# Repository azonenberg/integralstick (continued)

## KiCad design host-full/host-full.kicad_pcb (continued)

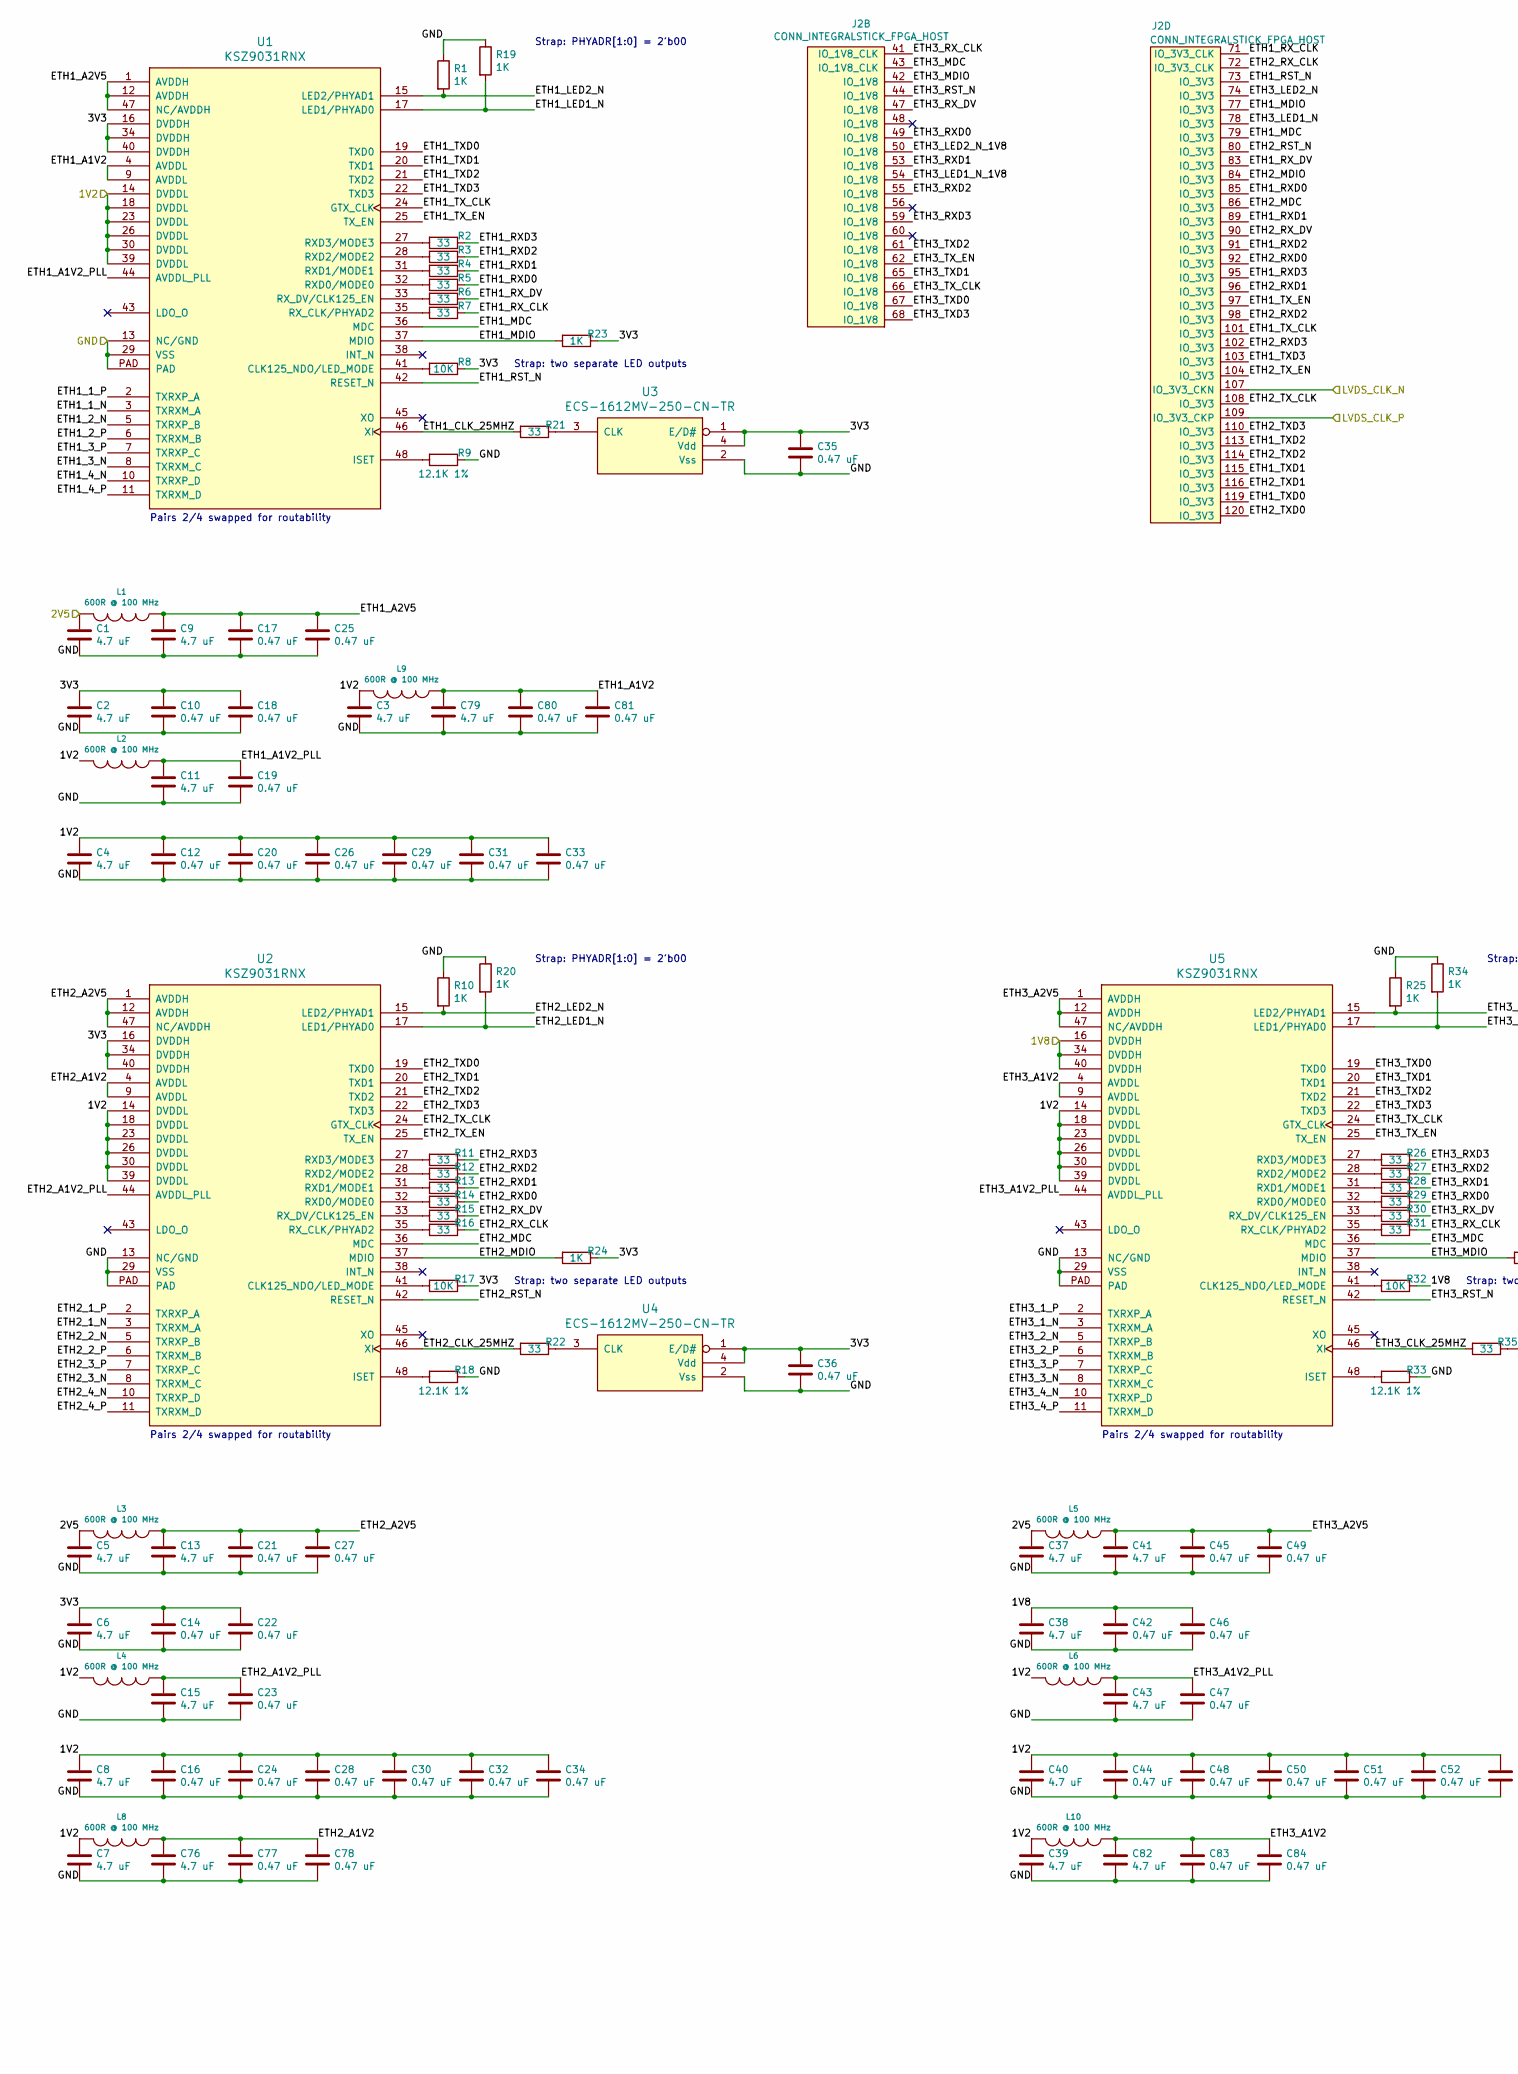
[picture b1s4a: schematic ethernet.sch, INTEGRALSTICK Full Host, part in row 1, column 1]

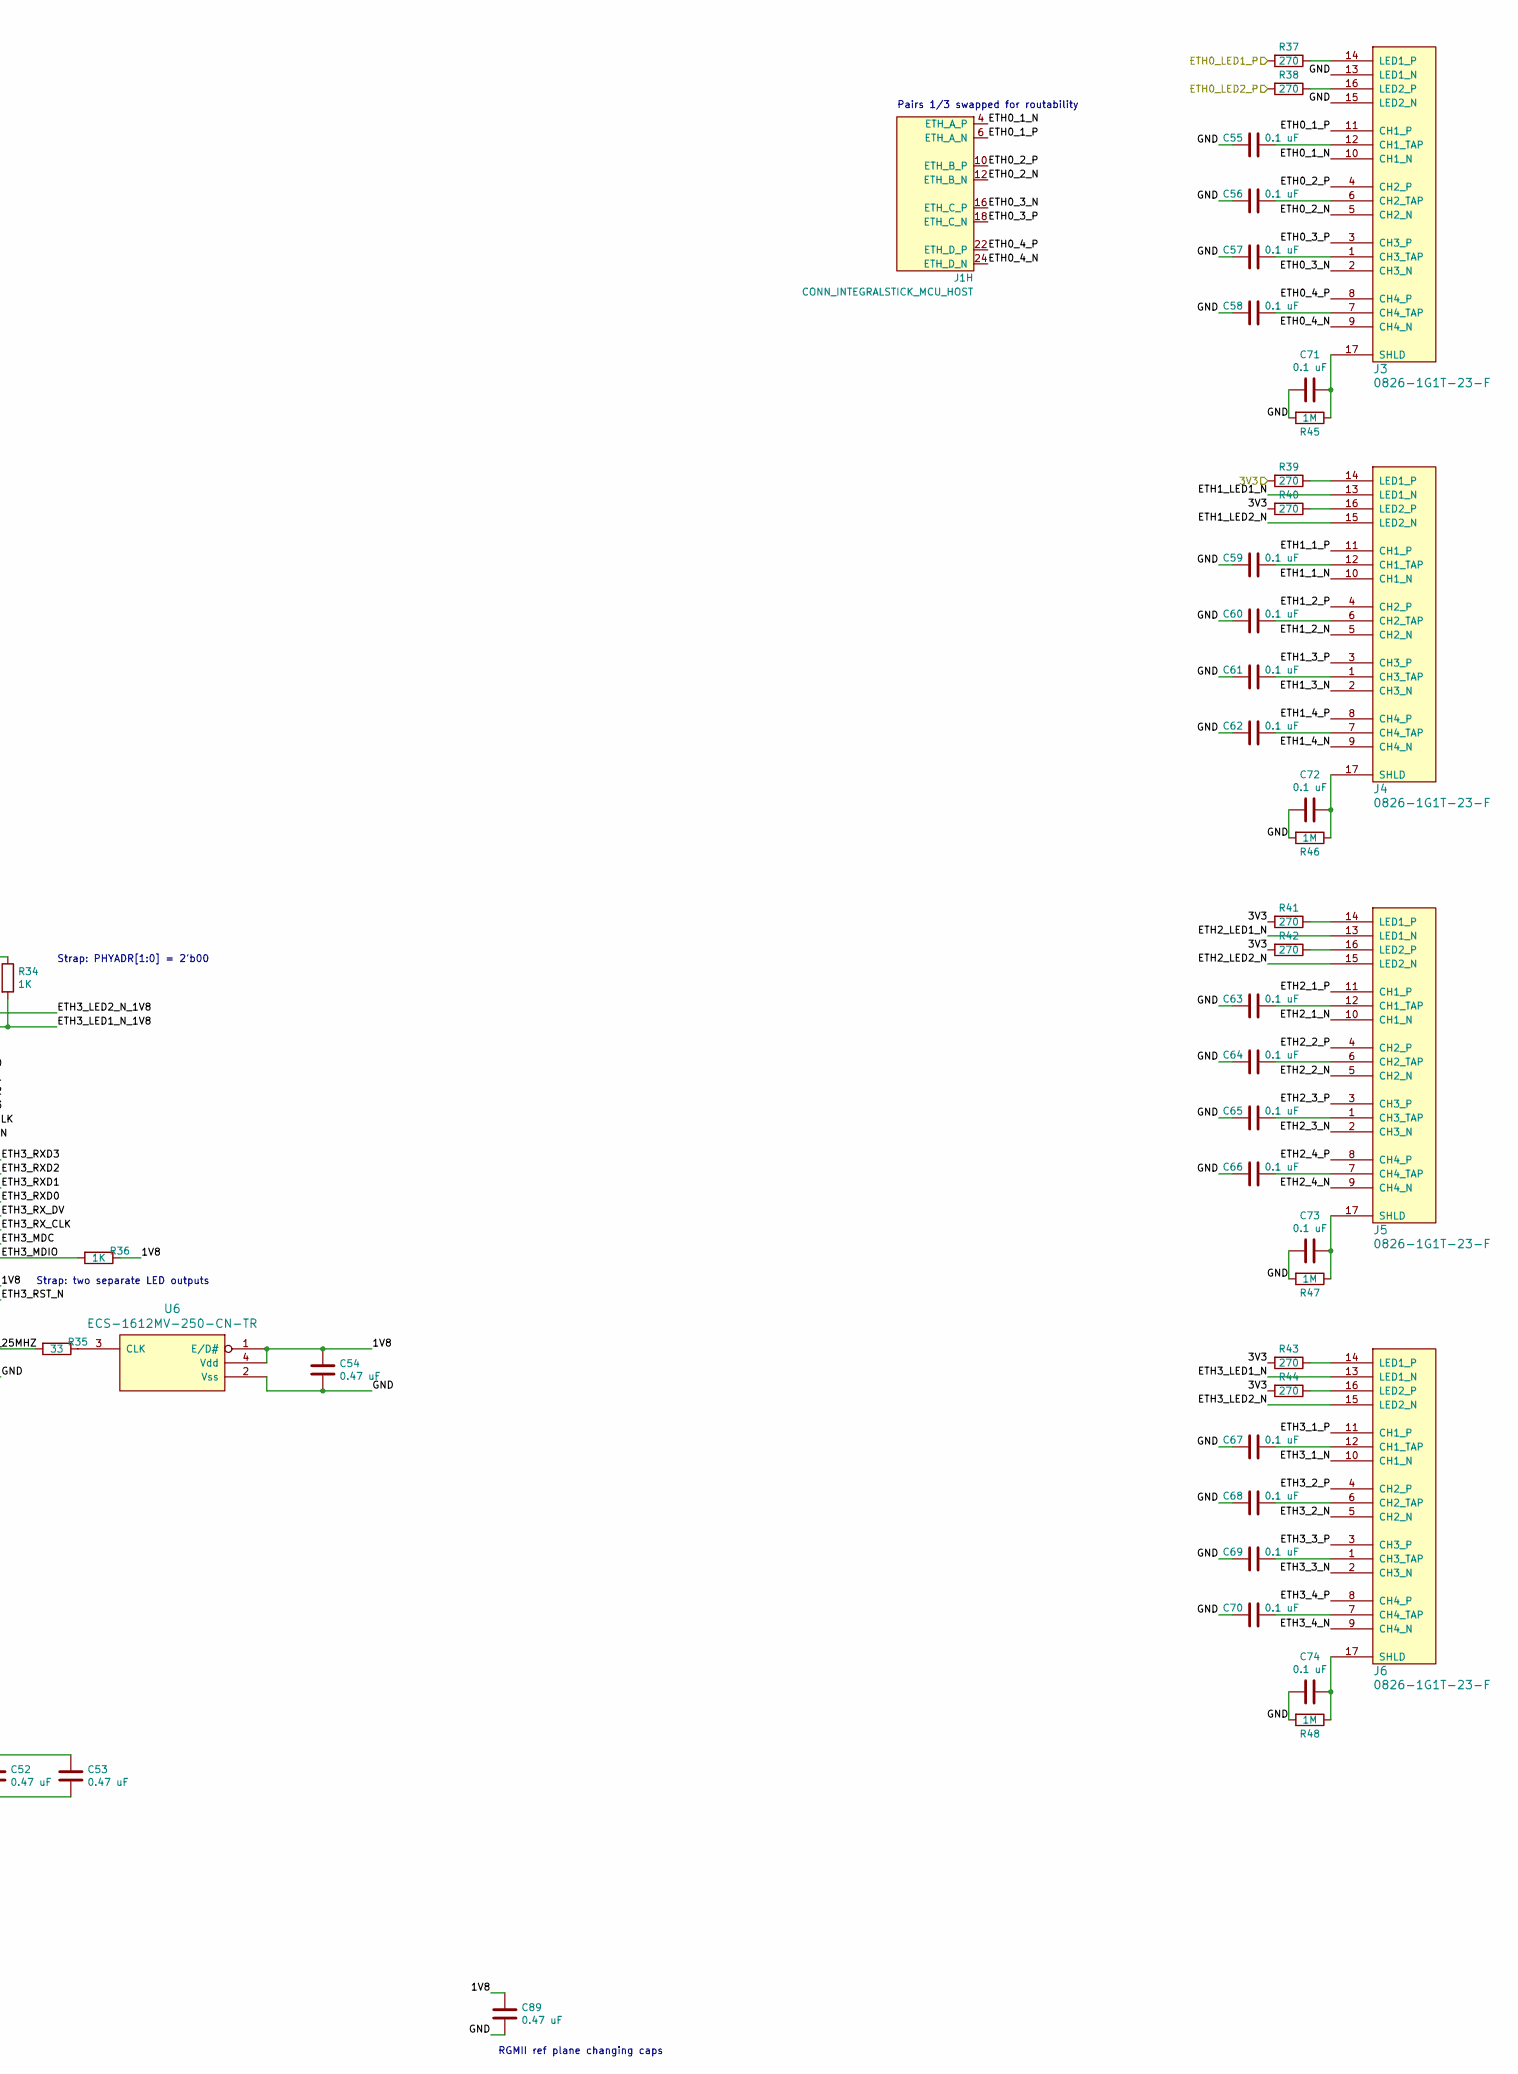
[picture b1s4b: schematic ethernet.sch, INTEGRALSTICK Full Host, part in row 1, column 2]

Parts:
C1, C2, C3, C4, C5, C6, C7, C8, C9, C11, C13, C15, C37, C38, C39, C40, C41, C43, C76, C79, C82: 4.7 uF; EIA_0603_CAP_NOSILK
C10, C12, C14, C16, C17, C18, C19, C20, C21, C22, C23, C24, C25, C26, C27, C28, C29, C30, C31, C32, C33, C34, C35, C36, C42, C44, C45, C46, C47, C48, C49, C50, C51, C52, C53, C54, C77, C78, C80, C81, C83, C84, C89: 0.47 uF; EIA_0402_CAP_NOSILK
C55, C56, C57, C58, C59, C60, C61, C62, C63, C64, C65, C66, C67, C68, C69, C70, C71, C72, C73, C74: 0.1 uF; EIA_0402_CAP_NOSILK
J1: CONN_INTEGRALSTICK_MCU_HOST; CONN_SAMTEC_QSH-060-01-L-D-A
J2: CONN_INTEGRALSTICK_FPGA_HOST; CONN_SAMTEC_QSH-060-01-L-D-A
J3, J4, J5, J6: 0826-1G1T-23-F; CONN_BELFUSE_0826_1G1T_23_F
L1, L2, L3, L4, L5, L6, L8, L9, L10: 600R @ 100 MHz; EIA_0402_CAP_NOSILK
R1, R10, R19, R20, R23, R24, R25, R34, R36: 1K; EIA_0402_RES_NOSILK
R2, R3, R4, R5, R6, R7, R11, R12, R13, R14, R15, R16, R21, R22, R26, R27, R28, R29, R30, R31, R35: 33; EIA_0402_RES_NOSILK
R8, R17, R32: 10K; EIA_0402_RES_NOSILK
R9, R18, R33: 12.1K 1%; EIA_0402_RES_NOSILK
R37, R38, R39, R40, R41, R42, R43, R44: 270; EIA_0402_RES_NOSILK
R45, R46, R47, R48: 1M; EIA_0402_RES_NOSILK
U1, U2, U5: KSZ9031RNX; QFN_48_0.5MM_7x7MM
U3, U4, U6: ECS-1612MV-250-CN-TR; OSCILLATOR_1.6x1.2

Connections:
/1V2: C3.1, C4.1, C7.1, C8.1, C12.1, C16.1, C20.1, C24.1, C26.1, C28.1, C29.1, C30.1, C31.1, C32.1, C33.1, C34.1, C39.1, C40.1, C44.1, C48.1, C50.1, C51.1, C52.1, C53.1, L2.2, L4.2, L6.2, L8.2, L9.2, L10.2, U1.14 (DVDDL), U1.18 (DVDDL), U1.23 (DVDDL), U1.26 (DVDDL), U1.30 (DVDDL), U1.39 (DVDDL), U2.14 (DVDDL), U2.18 (DVDDL), U2.23 (DVDDL), U2.26 (DVDDL), U2.30 (DVDDL), U2.39 (DVDDL), U5.14 (DVDDL), U5.18 (DVDDL), U5.23 (DVDDL), U5.26 (DVDDL), U5.30 (DVDDL), U5.39 (DVDDL); also elsewhere on the board
/1V8: C38.1, C42.1, C46.1, C54.1, C89.1, R32.1, R36.1, U5.16 (DVDDH), U5.34 (DVDDH), U5.40 (DVDDH), U6.1 (E/D#), U6.4 (Vdd); also elsewhere on the board
/2V5: C1.1, C5.1, C37.1, L1.2, L3.2, L5.2; also elsewhere on the board
/3V3: C2.1, C6.1, C10.1, C14.1, C18.1, C22.1, C35.1, C36.1, R8.1, R17.1, R23.1, R24.1, R39.2, R40.2, R41.2, R42.2, R43.2, R44.2, U1.16 (DVDDH), U1.34 (DVDDH), U1.40 (DVDDH), U2.16 (DVDDH), U2.34 (DVDDH), U2.40 (DVDDH), U3.1 (E/D#), U3.4 (Vdd), U4.1 (E/D#), U4.4 (Vdd); also elsewhere on the board
/ETH0_LED1_P: R37.2; also elsewhere on the board
/ETH0_LED2_P: R38.2; also elsewhere on the board
/Ethernet/ETH0_1_N: J1.4 (ETH_A_P), J3.10 (CH1_N)
/Ethernet/ETH0_1_P: J1.6 (ETH_A_N), J3.11 (CH1_P)
/Ethernet/ETH0_2_N: J1.12 (ETH_B_N), J3.5 (CH2_N)
/Ethernet/ETH0_2_P: J1.10 (ETH_B_P), J3.4 (CH2_P)
/Ethernet/ETH0_3_N: J1.16 (ETH_C_P), J3.2 (CH3_N)
/Ethernet/ETH0_3_P: J1.18 (ETH_C_N), J3.3 (CH3_P)
/Ethernet/ETH0_4_N: J1.24 (ETH_D_N), J3.9 (CH4_N)
/Ethernet/ETH0_4_P: J1.22 (ETH_D_P), J3.8 (CH4_P)
/Ethernet/ETH1_1_N: J4.10 (CH1_N), U1.3 (TXRXM_A)
/Ethernet/ETH1_1_P: J4.11 (CH1_P), U1.2 (TXRXP_A)
/Ethernet/ETH1_2_N: J4.5 (CH2_N), U1.5 (TXRXP_B)
/Ethernet/ETH1_2_P: J4.4 (CH2_P), U1.6 (TXRXM_B)
/Ethernet/ETH1_3_N: J4.2 (CH3_N), U1.8 (TXRXM_C)
/Ethernet/ETH1_3_P: J4.3 (CH3_P), U1.7 (TXRXP_C)
/Ethernet/ETH1_4_N: J4.9 (CH4_N), U1.10 (TXRXP_D)
/Ethernet/ETH1_4_P: J4.8 (CH4_P), U1.11 (TXRXM_D)
/Ethernet/ETH1_A1V2: C79.1, C80.1, C81.1, L9.1, U1.4 (AVDDL), U1.9 (AVDDL)
/Ethernet/ETH1_A1V2_PLL: C11.1, C19.1, L2.1, U1.44 (AVDDL_PLL)
/Ethernet/ETH1_A2V5: C9.1, C17.1, C25.1, L1.1, U1.1 (AVDDH), U1.12 (AVDDH), U1.47 (NC/AVDDH)
/Ethernet/ETH1_CLK_25MHZ: R21.2, U1.46 (XI)
/Ethernet/ETH1_LED1_N: J4.13 (LED1_N), R19.2, U1.17 (LED1/PHYAD0)
/Ethernet/ETH1_LED2_N: J4.15 (LED2_N), R1.2, U1.15 (LED2/PHYAD1)
/Ethernet/ETH1_MDC: J2.79 (IO_3V3), U1.36 (MDC)
/Ethernet/ETH1_MDIO: J2.77 (IO_3V3), R23.2, U1.37 (MDIO)
/Ethernet/ETH1_RST_N: J2.73 (IO_3V3), U1.42 (RESET_N)
/Ethernet/ETH1_RXD0: J2.85 (IO_3V3), R5.1
/Ethernet/ETH1_RXD1: J2.89 (IO_3V3), R4.1
/Ethernet/ETH1_RXD2: J2.91 (IO_3V3), R3.1
/Ethernet/ETH1_RXD3: J2.95 (IO_3V3), R2.1
/Ethernet/ETH1_RX_CLK: J2.71 (IO_3V3_CLK), R7.1
/Ethernet/ETH1_RX_DV: J2.83 (IO_3V3), R6.1
/Ethernet/ETH1_TXD0: J2.119 (IO_3V3), U1.19 (TXD0)
/Ethernet/ETH1_TXD1: J2.115 (IO_3V3), U1.20 (TXD1)
/Ethernet/ETH1_TXD2: J2.113 (IO_3V3), U1.21 (TXD2)
/Ethernet/ETH1_TXD3: J2.103 (IO_3V3), U1.22 (TXD3)
/Ethernet/ETH1_TX_CLK: J2.101 (IO_3V3), U1.24 (GTX_CLK)
/Ethernet/ETH1_TX_EN: J2.97 (IO_3V3), U1.25 (TX_EN)
/Ethernet/ETH2_1_N: J5.10 (CH1_N), U2.3 (TXRXM_A)
/Ethernet/ETH2_1_P: J5.11 (CH1_P), U2.2 (TXRXP_A)
/Ethernet/ETH2_2_N: J5.5 (CH2_N), U2.5 (TXRXP_B)
/Ethernet/ETH2_2_P: J5.4 (CH2_P), U2.6 (TXRXM_B)
/Ethernet/ETH2_3_N: J5.2 (CH3_N), U2.8 (TXRXM_C)
/Ethernet/ETH2_3_P: J5.3 (CH3_P), U2.7 (TXRXP_C)
/Ethernet/ETH2_4_N: J5.9 (CH4_N), U2.10 (TXRXP_D)
/Ethernet/ETH2_4_P: J5.8 (CH4_P), U2.11 (TXRXM_D)
/Ethernet/ETH2_A1V2: C76.1, C77.1, C78.1, L8.1, U2.4 (AVDDL), U2.9 (AVDDL)
/Ethernet/ETH2_A1V2_PLL: C15.1, C23.1, L4.1, U2.44 (AVDDL_PLL)
/Ethernet/ETH2_A2V5: C13.1, C21.1, C27.1, L3.1, U2.1 (AVDDH), U2.12 (AVDDH), U2.47 (NC/AVDDH)
/Ethernet/ETH2_CLK_25MHZ: R22.2, U2.46 (XI)
/Ethernet/ETH2_LED1_N: J5.13 (LED1_N), R20.2, U2.17 (LED1/PHYAD0)
/Ethernet/ETH2_LED2_N: J5.15 (LED2_N), R10.2, U2.15 (LED2/PHYAD1)
/Ethernet/ETH2_MDC: J2.86 (IO_3V3), U2.36 (MDC)
/Ethernet/ETH2_MDIO: J2.84 (IO_3V3), R24.2, U2.37 (MDIO)
/Ethernet/ETH2_RST_N: J2.80 (IO_3V3), U2.42 (RESET_N)
/Ethernet/ETH2_RXD0: J2.92 (IO_3V3), R14.1
/Ethernet/ETH2_RXD1: J2.96 (IO_3V3), R13.1
/Ethernet/ETH2_RXD2: J2.98 (IO_3V3), R12.1
/Ethernet/ETH2_RXD3: J2.102 (IO_3V3), R11.1
/Ethernet/ETH2_RX_CLK: J2.72 (IO_3V3_CLK), R16.1
/Ethernet/ETH2_RX_DV: J2.90 (IO_3V3), R15.1
/Ethernet/ETH2_TXD0: J2.120 (IO_3V3), U2.19 (TXD0)
/Ethernet/ETH2_TXD1: J2.116 (IO_3V3), U2.20 (TXD1)
/Ethernet/ETH2_TXD2: J2.114 (IO_3V3), U2.21 (TXD2)
/Ethernet/ETH2_TXD3: J2.110 (IO_3V3), U2.22 (TXD3)
/Ethernet/ETH2_TX_CLK: J2.108 (IO_3V3), U2.24 (GTX_CLK)
/Ethernet/ETH2_TX_EN: J2.104 (IO_3V3), U2.25 (TX_EN)
/Ethernet/ETH3_1_N: J6.10 (CH1_N), U5.3 (TXRXM_A)
/Ethernet/ETH3_1_P: J6.11 (CH1_P), U5.2 (TXRXP_A)
/Ethernet/ETH3_2_N: J6.5 (CH2_N), U5.5 (TXRXP_B)
/Ethernet/ETH3_2_P: J6.4 (CH2_P), U5.6 (TXRXM_B)
/Ethernet/ETH3_3_N: J6.2 (CH3_N), U5.8 (TXRXM_C)
/Ethernet/ETH3_3_P: J6.3 (CH3_P), U5.7 (TXRXP_C)
/Ethernet/ETH3_4_N: J6.9 (CH4_N), U5.10 (TXRXP_D)
/Ethernet/ETH3_4_P: J6.8 (CH4_P), U5.11 (TXRXM_D)
/Ethernet/ETH3_A1V2: C82.1, C83.1, C84.1, L10.1, U5.4 (AVDDL), U5.9 (AVDDL)
/Ethernet/ETH3_A1V2_PLL: C43.1, C47.1, L6.1, U5.44 (AVDDL_PLL)
/Ethernet/ETH3_A2V5: C41.1, C45.1, C49.1, L5.1, U5.1 (AVDDH), U5.12 (AVDDH), U5.47 (NC/AVDDH)
/Ethernet/ETH3_CLK_25MHZ: R35.2, U5.46 (XI)
/Ethernet/ETH3_LED1_N: J2.78 (IO_3V3), J6.13 (LED1_N)
/Ethernet/ETH3_LED1_N_1V8: J2.54 (IO_1V8), R34.2, U5.17 (LED1/PHYAD0)
/Ethernet/ETH3_LED2_N: J2.74 (IO_3V3), J6.15 (LED2_N)
/Ethernet/ETH3_LED2_N_1V8: J2.50 (IO_1V8), R25.2, U5.15 (LED2/PHYAD1)
/Ethernet/ETH3_MDC: J2.43 (IO_1V8_CLK), U5.36 (MDC)
/Ethernet/ETH3_MDIO: J2.42 (IO_1V8), R36.2, U5.37 (MDIO)
/Ethernet/ETH3_RST_N: J2.44 (IO_1V8), U5.42 (RESET_N)
/Ethernet/ETH3_RXD0: J2.49 (IO_1V8), R29.1
/Ethernet/ETH3_RXD1: J2.53 (IO_1V8), R28.1
/Ethernet/ETH3_RXD2: J2.55 (IO_1V8), R27.1
/Ethernet/ETH3_RXD3: J2.59 (IO_1V8), R26.1
/Ethernet/ETH3_RX_CLK: J2.41 (IO_1V8_CLK), R31.1
/Ethernet/ETH3_RX_DV: J2.47 (IO_1V8), R30.1
/Ethernet/ETH3_TXD0: J2.67 (IO_1V8), U5.19 (TXD0)
/Ethernet/ETH3_TXD1: J2.65 (IO_1V8), U5.20 (TXD1)
/Ethernet/ETH3_TXD2: J2.61 (IO_1V8), U5.21 (TXD2)
/Ethernet/ETH3_TXD3: J2.68 (IO_1V8), U5.22 (TXD3)
/Ethernet/ETH3_TX_CLK: J2.66 (IO_1V8), U5.24 (GTX_CLK)
/Ethernet/ETH3_TX_EN: J2.62 (IO_1V8), U5.25 (TX_EN)
/GND: C1.2, C2.2, C3.2, C4.2, C5.2, C6.2, C7.2, C8.2, C9.2, C10.2, C11.2, C12.2, C13.2, C14.2, C15.2, C16.2, C17.2, C18.2, C19.2, C20.2, C21.2, C22.2, C23.2, C24.2, C25.2, C26.2, C27.2, C28.2, C29.2, C30.2, C31.2, C32.2, C33.2, C34.2, C35.2, C36.2, C37.2, C38.2, C39.2, C40.2, C41.2, C42.2, C43.2, C44.2, C45.2, C46.2, C47.2, C48.2, C49.2, C50.2, C51.2, C52.2, C53.2, C54.2, C55.2, C56.2, C57.2, C58.2, C59.2, C60.2, C61.2, C62.2, C63.2, C64.2, C65.2, C66.2, C67.2, C68.2, C69.2, C70.2, C71.2, C72.2, C73.2, C74.2, C76.2, C77.2, C78.2, C79.2, C80.2, C81.2, C82.2, C83.2, C84.2, C89.2, J3.13 (LED1_N), J3.15 (LED2_N), R1.1, R9.1, R10.1, R18.1, R19.1, R20.1, R25.1, R33.1, R34.1, R45.2, R46.2, R47.2, R48.2, U1.13 (NC/GND), U1.29 (VSS), U1.PAD, U2.13 (NC/GND), U2.29 (VSS), U2.PAD, U3.2 (Vss), U4.2 (Vss), U5.13 (NC/GND), U5.29 (VSS), U5.PAD, U6.2 (Vss); also elsewhere on the board
/LVDS_CLK_N: J2.107 (IO_3V3_CKN); also elsewhere on the board
/LVDS_CLK_P: J2.109 (IO_3V3_CKP); also elsewhere on the board
unnamed: C55.1, J3.12 (CH1_TAP)
unnamed: C56.1, J3.6 (CH2_TAP)
unnamed: C57.1, J3.1 (CH3_TAP)
unnamed: C58.1, J3.7 (CH4_TAP)
unnamed: C59.1, J4.12 (CH1_TAP)
unnamed: C60.1, J4.6 (CH2_TAP)
unnamed: C61.1, J4.1 (CH3_TAP)
unnamed: C62.1, J4.7 (CH4_TAP)
unnamed: C63.1, J5.12 (CH1_TAP)
unnamed: C64.1, J5.6 (CH2_TAP)
unnamed: C65.1, J5.1 (CH3_TAP)
unnamed: C66.1, J5.7 (CH4_TAP)
unnamed: C67.1, J6.12 (CH1_TAP)
unnamed: C68.1, J6.6 (CH2_TAP)
unnamed: C69.1, J6.1 (CH3_TAP)
unnamed: C70.1, J6.7 (CH4_TAP)
unnamed: C71.1, J3.17 (SHLD), R45.1
unnamed: C72.1, J4.17 (SHLD), R46.1
unnamed: C73.1, J5.17 (SHLD), R47.1
unnamed: C74.1, J6.17 (SHLD), R48.1
unnamed: J3.14 (LED1_P), R37.1
unnamed: J3.16 (LED2_P), R38.1
unnamed: J4.14 (LED1_P), R39.1
unnamed: J4.16 (LED2_P), R40.1
unnamed: J5.14 (LED1_P), R41.1
unnamed: J5.16 (LED2_P), R42.1
unnamed: J6.14 (LED1_P), R43.1
unnamed: J6.16 (LED2_P), R44.1
unnamed: R2.2, U1.27 (RXD3/MODE3)
unnamed: R3.2, U1.28 (RXD2/MODE2)
unnamed: R4.2, U1.31 (RXD1/MODE1)
unnamed: R5.2, U1.32 (RXD0/MODE0)
unnamed: R6.2, U1.33 (RX_DV/CLK125_EN)
unnamed: R7.2, U1.35 (RX_CLK/PHYAD2)
unnamed: R8.2, U1.41 (CLK125_NDO/LED_MODE)
unnamed: R9.2, U1.48 (ISET)
unnamed: R11.2, U2.27 (RXD3/MODE3)
unnamed: R12.2, U2.28 (RXD2/MODE2)
unnamed: R13.2, U2.31 (RXD1/MODE1)
unnamed: R14.2, U2.32 (RXD0/MODE0)
unnamed: R15.2, U2.33 (RX_DV/CLK125_EN)
unnamed: R16.2, U2.35 (RX_CLK/PHYAD2)
unnamed: R17.2, U2.41 (CLK125_NDO/LED_MODE)
unnamed: R18.2, U2.48 (ISET)
unnamed: R21.1, U3.3 (CLK)
unnamed: R22.1, U4.3 (CLK)
unnamed: R26.2, U5.27 (RXD3/MODE3)
unnamed: R27.2, U5.28 (RXD2/MODE2)
unnamed: R28.2, U5.31 (RXD1/MODE1)
unnamed: R29.2, U5.32 (RXD0/MODE0)
unnamed: R30.2, U5.33 (RX_DV/CLK125_EN)
unnamed: R31.2, U5.35 (RX_CLK/PHYAD2)
unnamed: R32.2, U5.41 (CLK125_NDO/LED_MODE)
unnamed: R33.2, U5.48 (ISET)
unnamed: R35.1, U6.3 (CLK)

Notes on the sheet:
Strap: PHYADR[1:0] = 2'b00
Strap: two separate LED outputs
Pairs 2/4 swapped for routability
Pairs 1/3 swapped for routability
RGMII ref plane changing caps

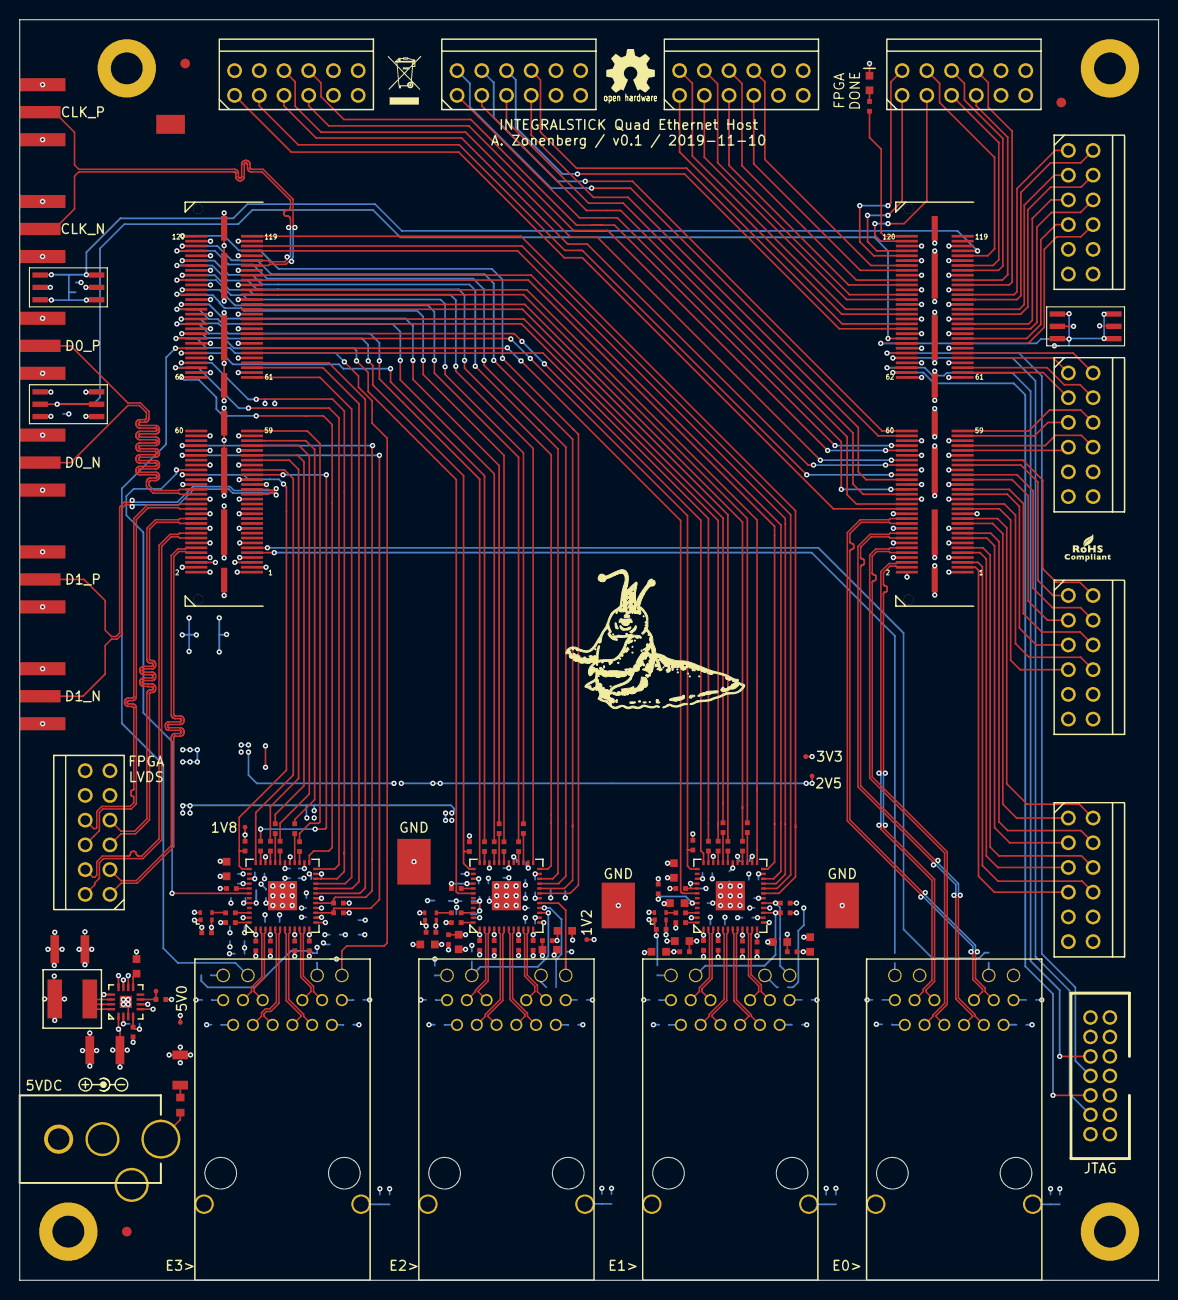
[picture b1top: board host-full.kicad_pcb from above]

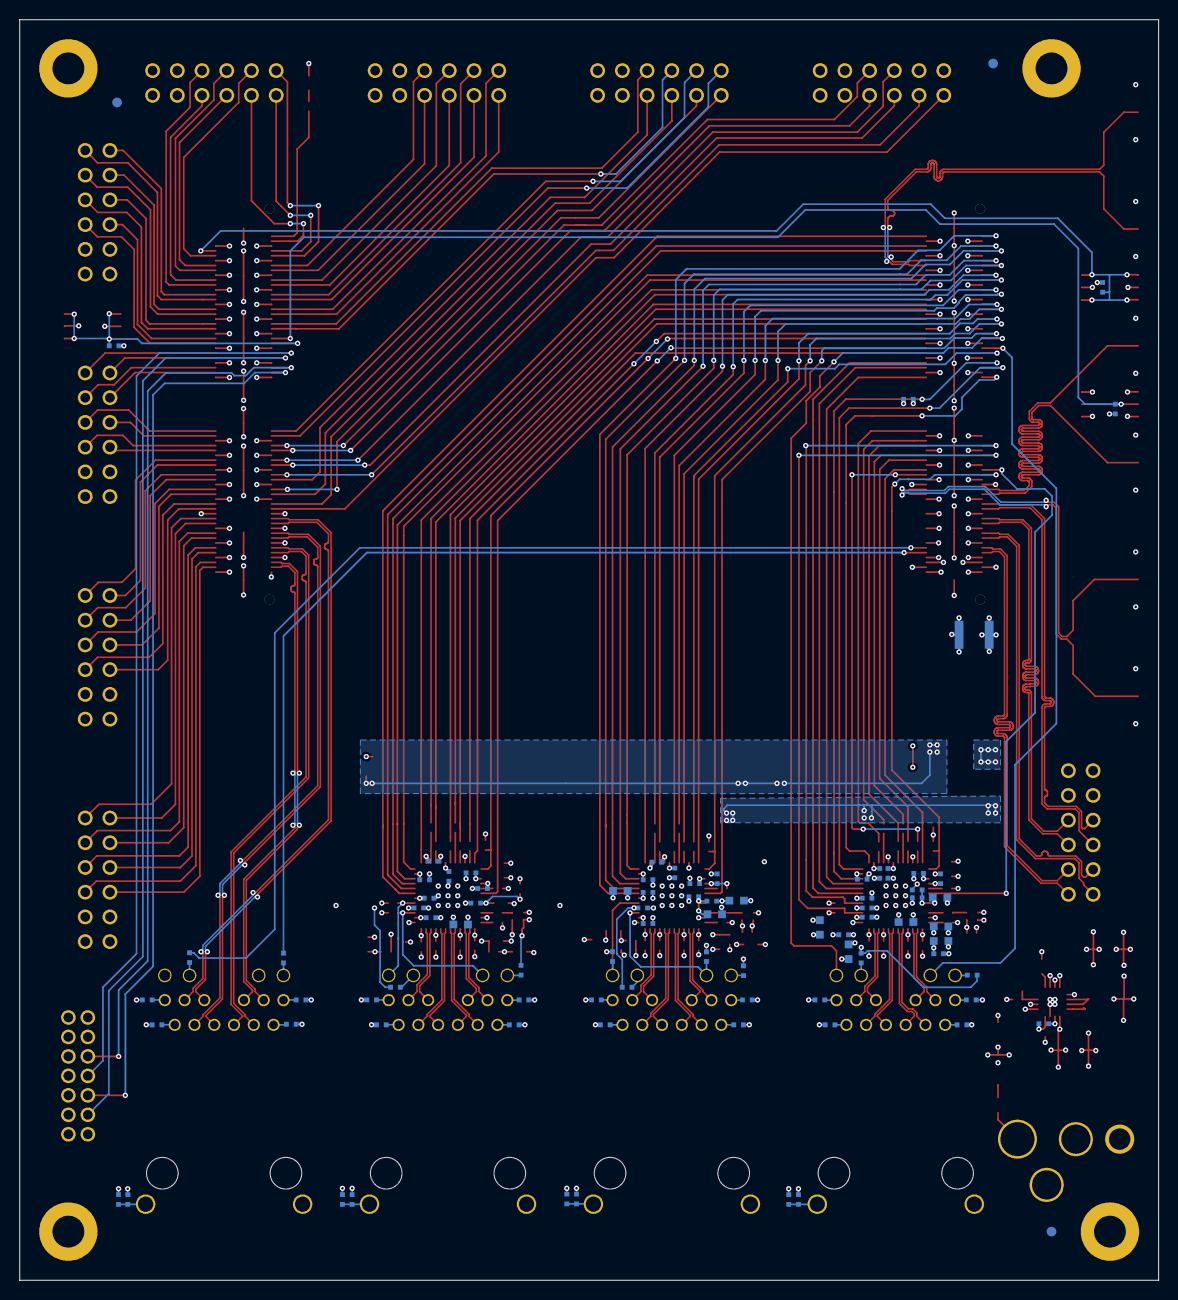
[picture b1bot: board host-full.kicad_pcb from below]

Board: 4 copper layers, 117.0 x 129.5 mm, 204 parts (84 on the bottom side), 251 nets.

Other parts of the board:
FIDUCIAL_1MM, FIDUCIAL_1MM#2, FIDUCIAL_1MM#3, FIDUCIAL_1MM#4, FIDUCIAL_1MM#5, FIDUCIAL_1MM#6: VAL**; FIDUCIAL_1MM

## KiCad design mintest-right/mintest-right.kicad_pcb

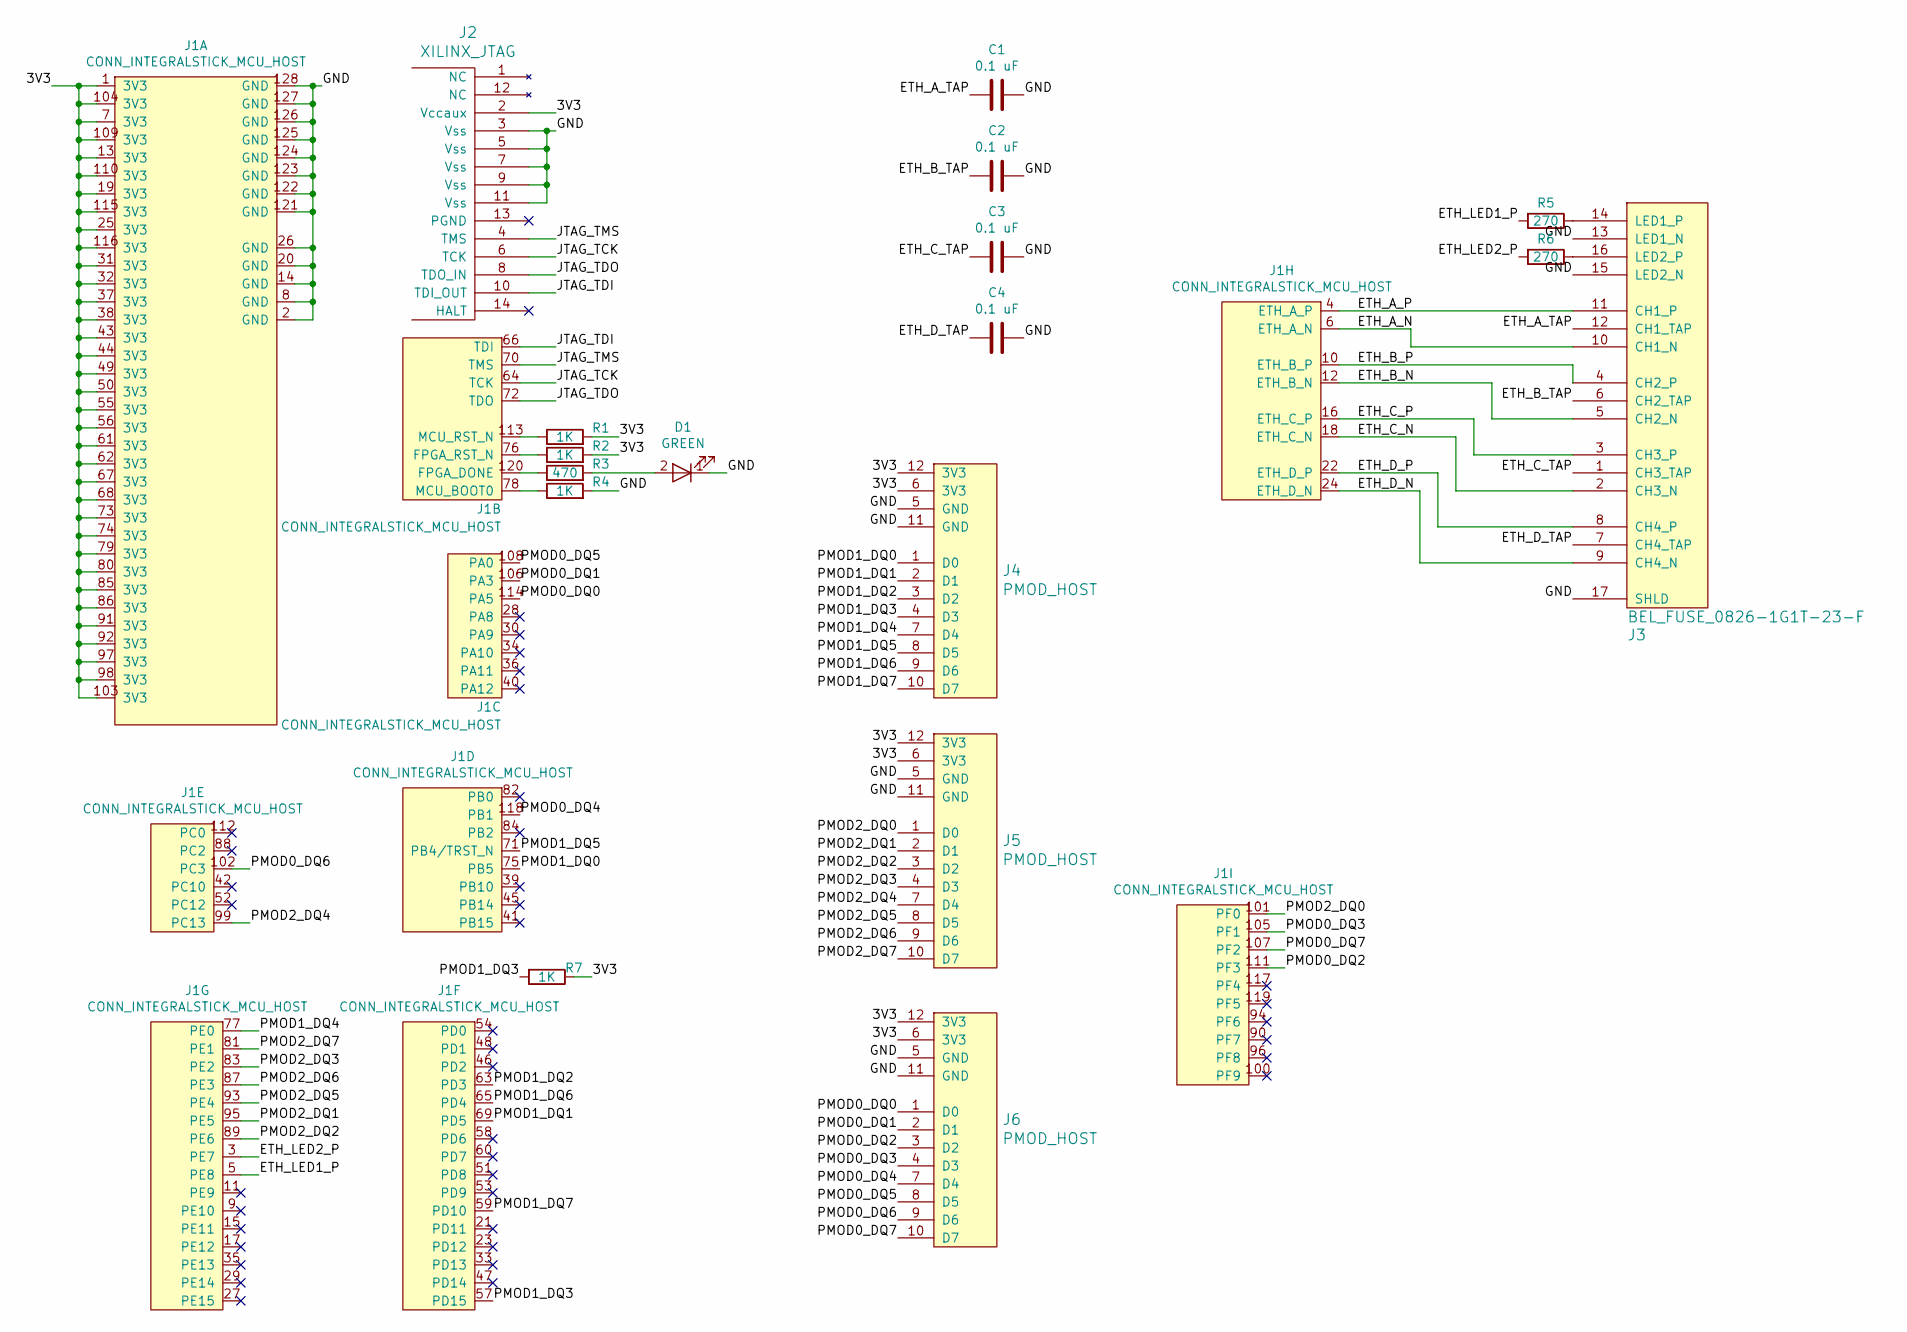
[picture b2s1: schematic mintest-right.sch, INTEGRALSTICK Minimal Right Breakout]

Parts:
C1, C2, C3, C4: 0.1 uF; EIA_0402_CAP_NOSILK
D1: GREEN; EIA_0603_LED
J1: CONN_INTEGRALSTICK_MCU_HOST; CONN_SAMTEC_QSH-060-01-L-D-A
J2: XILINX_JTAG; XILINX_JTAG_PTH_MOLEX_0878311420
J3: BEL_FUSE_0826-1G1T-23-F; CONN_BELFUSE_0826_1G1T_23_F
J4, J5, J6: PMOD_HOST; CONN_HEADER_2.54MM_2x6_RA_PMOD_HOST
R1, R2, R4, R7: 1K; EIA_0402_RES_NOSILK
R3: 470; EIA_0402_RES_NOSILK
R5, R6: 270; EIA_0402_RES_NOSILK

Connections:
/3V3: J1.1 (3V3), J1.7 (3V3), J1.13 (3V3), J1.19 (3V3), J1.25 (3V3), J1.31 (3V3), J1.32 (3V3), J1.37 (3V3), J1.38 (3V3), J1.43 (3V3), J1.44 (3V3), J1.49 (3V3), J1.50 (3V3), J1.55 (3V3), J1.56 (3V3), J1.61 (3V3), J1.62 (3V3), J1.67 (3V3), J1.68 (3V3), J1.73 (3V3), J1.74 (3V3), J1.79 (3V3), J1.80 (3V3), J1.85 (3V3), J1.86 (3V3), J1.91 (3V3), J1.92 (3V3), J1.97 (3V3), J1.98 (3V3), J1.103 (3V3), J1.104 (3V3), J1.109 (3V3), J1.110 (3V3), J1.115 (3V3), J1.116 (3V3), J2.2 (Vccaux), J4.6 (3V3), J4.12 (3V3), J5.6 (3V3), J5.12 (3V3), J6.6 (3V3), J6.12 (3V3), R1.2, R2.2, R7.1
/ETH_A_N: J1.6 (ETH_A_N), J3.10 (CH1_N)
/ETH_A_P: J1.4 (ETH_A_P), J3.11 (CH1_P)
/ETH_A_TAP: C1.2, J3.12 (CH1_TAP)
/ETH_B_N: J1.12 (ETH_B_N), J3.5 (CH2_N)
/ETH_B_P: J1.10 (ETH_B_P), J3.4 (CH2_P)
/ETH_B_TAP: C2.2, J3.6 (CH2_TAP)
/ETH_C_N: J1.18 (ETH_C_N), J3.2 (CH3_N)
/ETH_C_P: J1.16 (ETH_C_P), J3.3 (CH3_P)
/ETH_C_TAP: C3.2, J3.1 (CH3_TAP)
/ETH_D_N: J1.24 (ETH_D_N), J3.9 (CH4_N)
/ETH_D_P: J1.22 (ETH_D_P), J3.8 (CH4_P)
/ETH_D_TAP: C4.2, J3.7 (CH4_TAP)
/ETH_LED1_P: J1.5 (PE8), R5.2
/ETH_LED2_P: J1.3 (PE7), R6.2
/GND: C1.1, C2.1, C3.1, C4.1, D1.1 (K), J1.2 (GND), J1.8 (GND), J1.14 (GND), J1.20 (GND), J1.26 (GND), J1.121 (GND), J1.122 (GND), J1.123 (GND), J1.124 (GND), J1.125 (GND), J1.126 (GND), J1.127 (GND), J1.128 (GND), J2.3 (Vss), J2.5 (Vss), J2.7 (Vss), J2.9 (Vss), J2.11 (Vss), J3.13 (LED1_N), J3.15 (LED2_N), J3.17 (SHLD), J4.5 (GND), J4.11 (GND), J5.5 (GND), J5.11 (GND), J6.5 (GND), J6.11 (GND), R4.2
/JTAG_TCK: J1.64 (TCK), J2.6 (TCK)
/JTAG_TDI: J1.66 (TDI), J2.10 (TDI_OUT)
/JTAG_TDO: J1.72 (TDO), J2.8 (TDO_IN)
/JTAG_TMS: J1.70 (TMS), J2.4 (TMS)
/PMOD0_DQ0: J1.114 (PA5), J6.1 (D0)
/PMOD0_DQ1: J1.106 (PA3), J6.2 (D1)
/PMOD0_DQ2: J1.111 (PF3), J6.3 (D2)
/PMOD0_DQ3: J1.105 (PF1), J6.4 (D3)
/PMOD0_DQ4: J1.118 (PB1), J6.7 (D4)
/PMOD0_DQ5: J1.108 (PA0), J6.8 (D5)
/PMOD0_DQ6: J1.102 (PC3), J6.9 (D6)
/PMOD0_DQ7: J1.107 (PF2), J6.10 (D7)
/PMOD1_DQ0: J1.75 (PB5), J4.1 (D0)
/PMOD1_DQ1: J1.69 (PD5), J4.2 (D1)
/PMOD1_DQ2: J1.63 (PD3), J4.3 (D2)
/PMOD1_DQ3: J1.57 (PD15), J4.4 (D3), R7.2
/PMOD1_DQ4: J1.77 (PE0), J4.7 (D4)
/PMOD1_DQ5: J1.71 (PB4/TRST_N), J4.8 (D5)
/PMOD1_DQ6: J1.65 (PD4), J4.9 (D6)
/PMOD1_DQ7: J1.59 (PD10), J4.10 (D7)
/PMOD2_DQ0: J1.101 (PF0), J5.1 (D0)
/PMOD2_DQ1: J1.95 (PE5), J5.2 (D1)
/PMOD2_DQ2: J1.89 (PE6), J5.3 (D2)
/PMOD2_DQ3: J1.83 (PE2), J5.4 (D3)
/PMOD2_DQ4: J1.99 (PC13), J5.7 (D4)
/PMOD2_DQ5: J1.93 (PE4), J5.8 (D5)
/PMOD2_DQ6: J1.87 (PE3), J5.9 (D6)
/PMOD2_DQ7: J1.81 (PE1), J5.10 (D7)
unnamed: D1.2 (A), R3.2
unnamed: J1.76 (FPGA_RST_N), R2.1
unnamed: J1.78 (MCU_BOOT0), R4.1
unnamed: J1.113 (MCU_RST_N), R1.1
unnamed: J1.120 (FPGA_DONE), R3.1
unnamed: J3.14 (LED1_P), R5.1
unnamed: J3.16 (LED2_P), R6.1

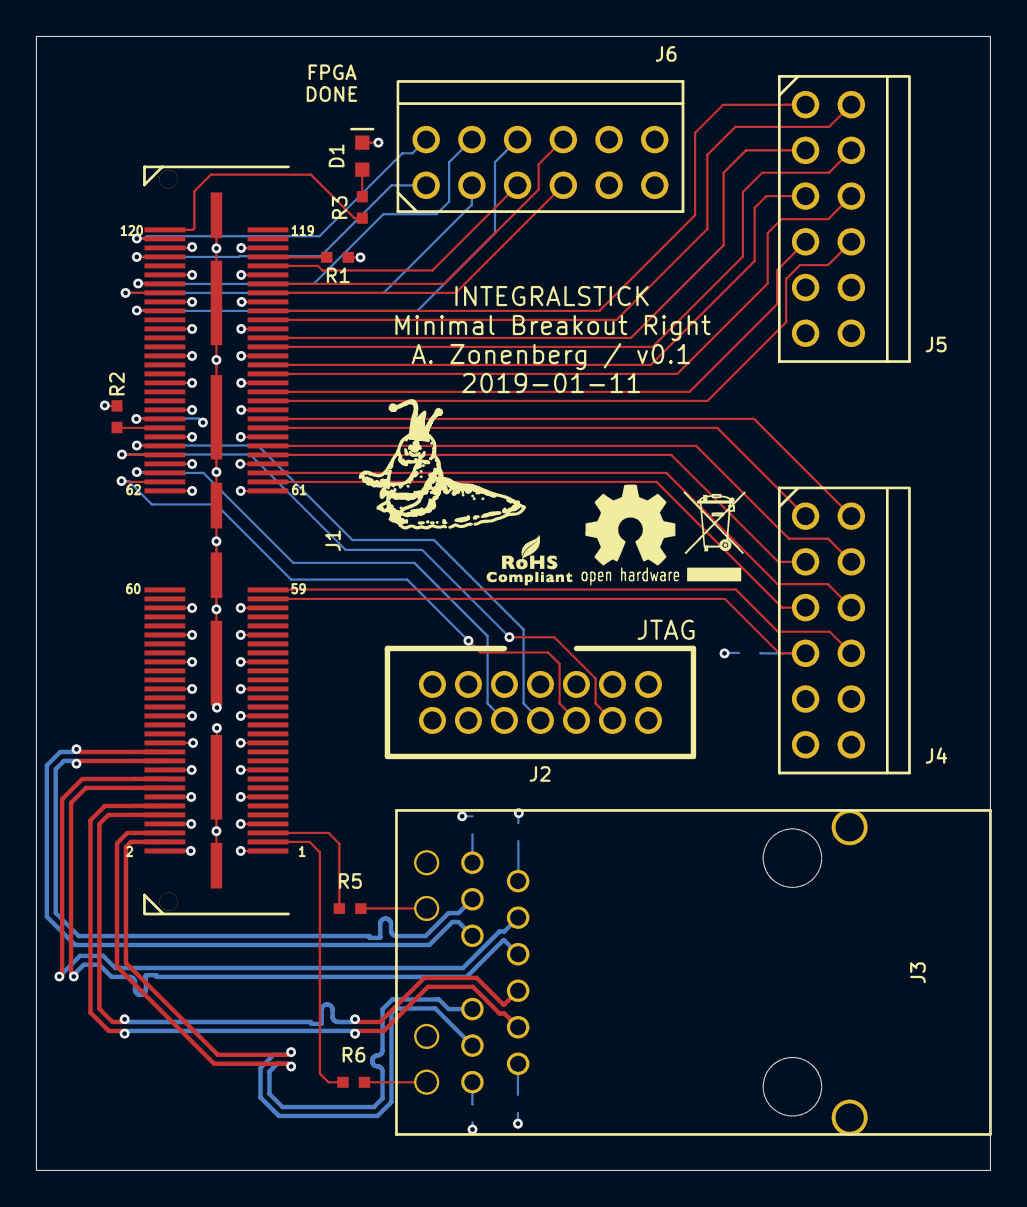
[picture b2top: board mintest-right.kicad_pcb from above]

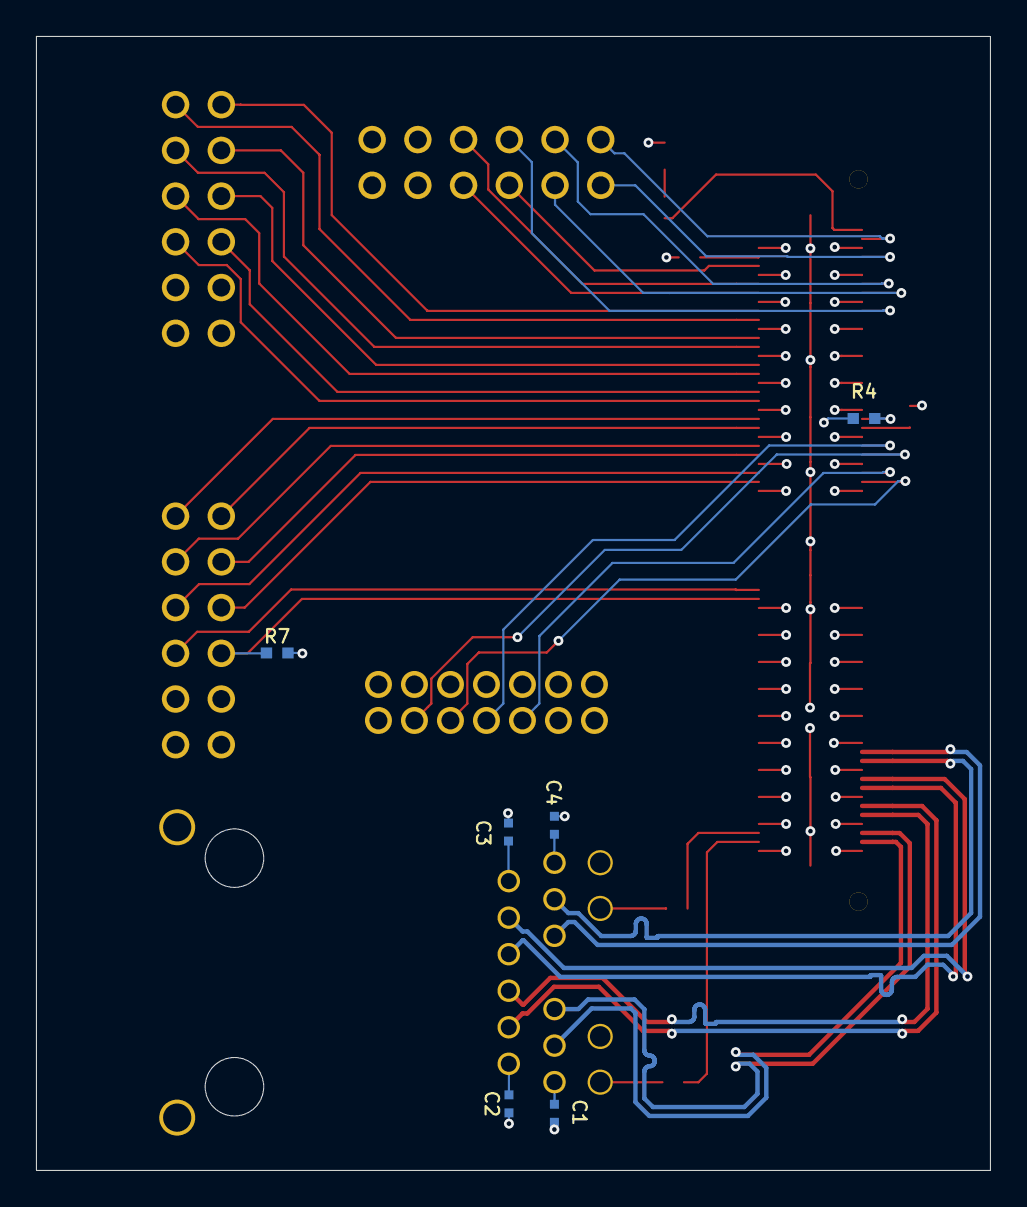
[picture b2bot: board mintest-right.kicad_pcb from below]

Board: 4 copper layers, 53.0 x 63.0 mm, 18 parts (6 on the bottom side), 51 nets.
